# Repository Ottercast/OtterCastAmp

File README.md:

# OtterCastAmp

OtterCastAmp is an open-source Sonos Amp replacement, based on a Sochip S3 SoC and pulseaudio sink/source.

## How do I get one?

We are currently planning a small batch production run, stay tuned.
[editors notes: It is 2024 now and noone really expected how bad covid would affect the supply chain. While all parts are available again, we are only slowly getting interested in this project again]

You don't want to wait? You can of course run a small batch on your own! Please have a look into the [gerber folder](/gerber_v1.2), a batch size of just 5 (and up to 30) boards is supported by JLC.

## Installation & Configuration

After [downloading and flashing](https://cast.otter.jetzt/docs/firmware/#download-ready-made-images) the image, OtterCastAmp can either be configured via the `config.ini` file or via the web-interface.

Check out our [Documentation](https://cast.otter.jetzt/docs/) for more information!

## Schematics?

[Schematics!](/schematic_V1.2/OtterCastAmp.pdf)

## Team

 - [@lucysrausch](https://bsky.app/profile/lucysrausch.bsky.social) Hardware - OtterCastAmp
 - [@_Jana_Marie](https://twitter.com/_Jana_Marie) Hardware - OtterCastAudio
 - [@Toble_Miner](https://twitter.com/Toble_Miner) Software - Embedded Linux
 - [@Manawyrm](https://twitter.com/Manawyrm) Software - Frontend & OTA

## Do you plan a PoE version?

Maybe.
(25W of power is not enough and >50W isn't popular)

## Status

HW v1.0 is ordered and we already found bugs fixed in v1.2 (not ordered yet)
Tested & working:

 - [x] Audio Speaker Out
 - [x] Audio Line In
 - [ ] Bluetooth Audio In
 - [x] USB PD
 - [x] WiFi
 - [x] Ethernet
 - [x] Display
 - [x] Uart

 - [x] Webinterface (config)
 - [x] Shairport-sync
 - [x] Pulseaudio sink
 - [x] Pulseaudio source
 - [x] snapcast

## License

Note: The following files or directories are excluded from the License and are otherwise licensed

 - 3D/
 - datasheets/

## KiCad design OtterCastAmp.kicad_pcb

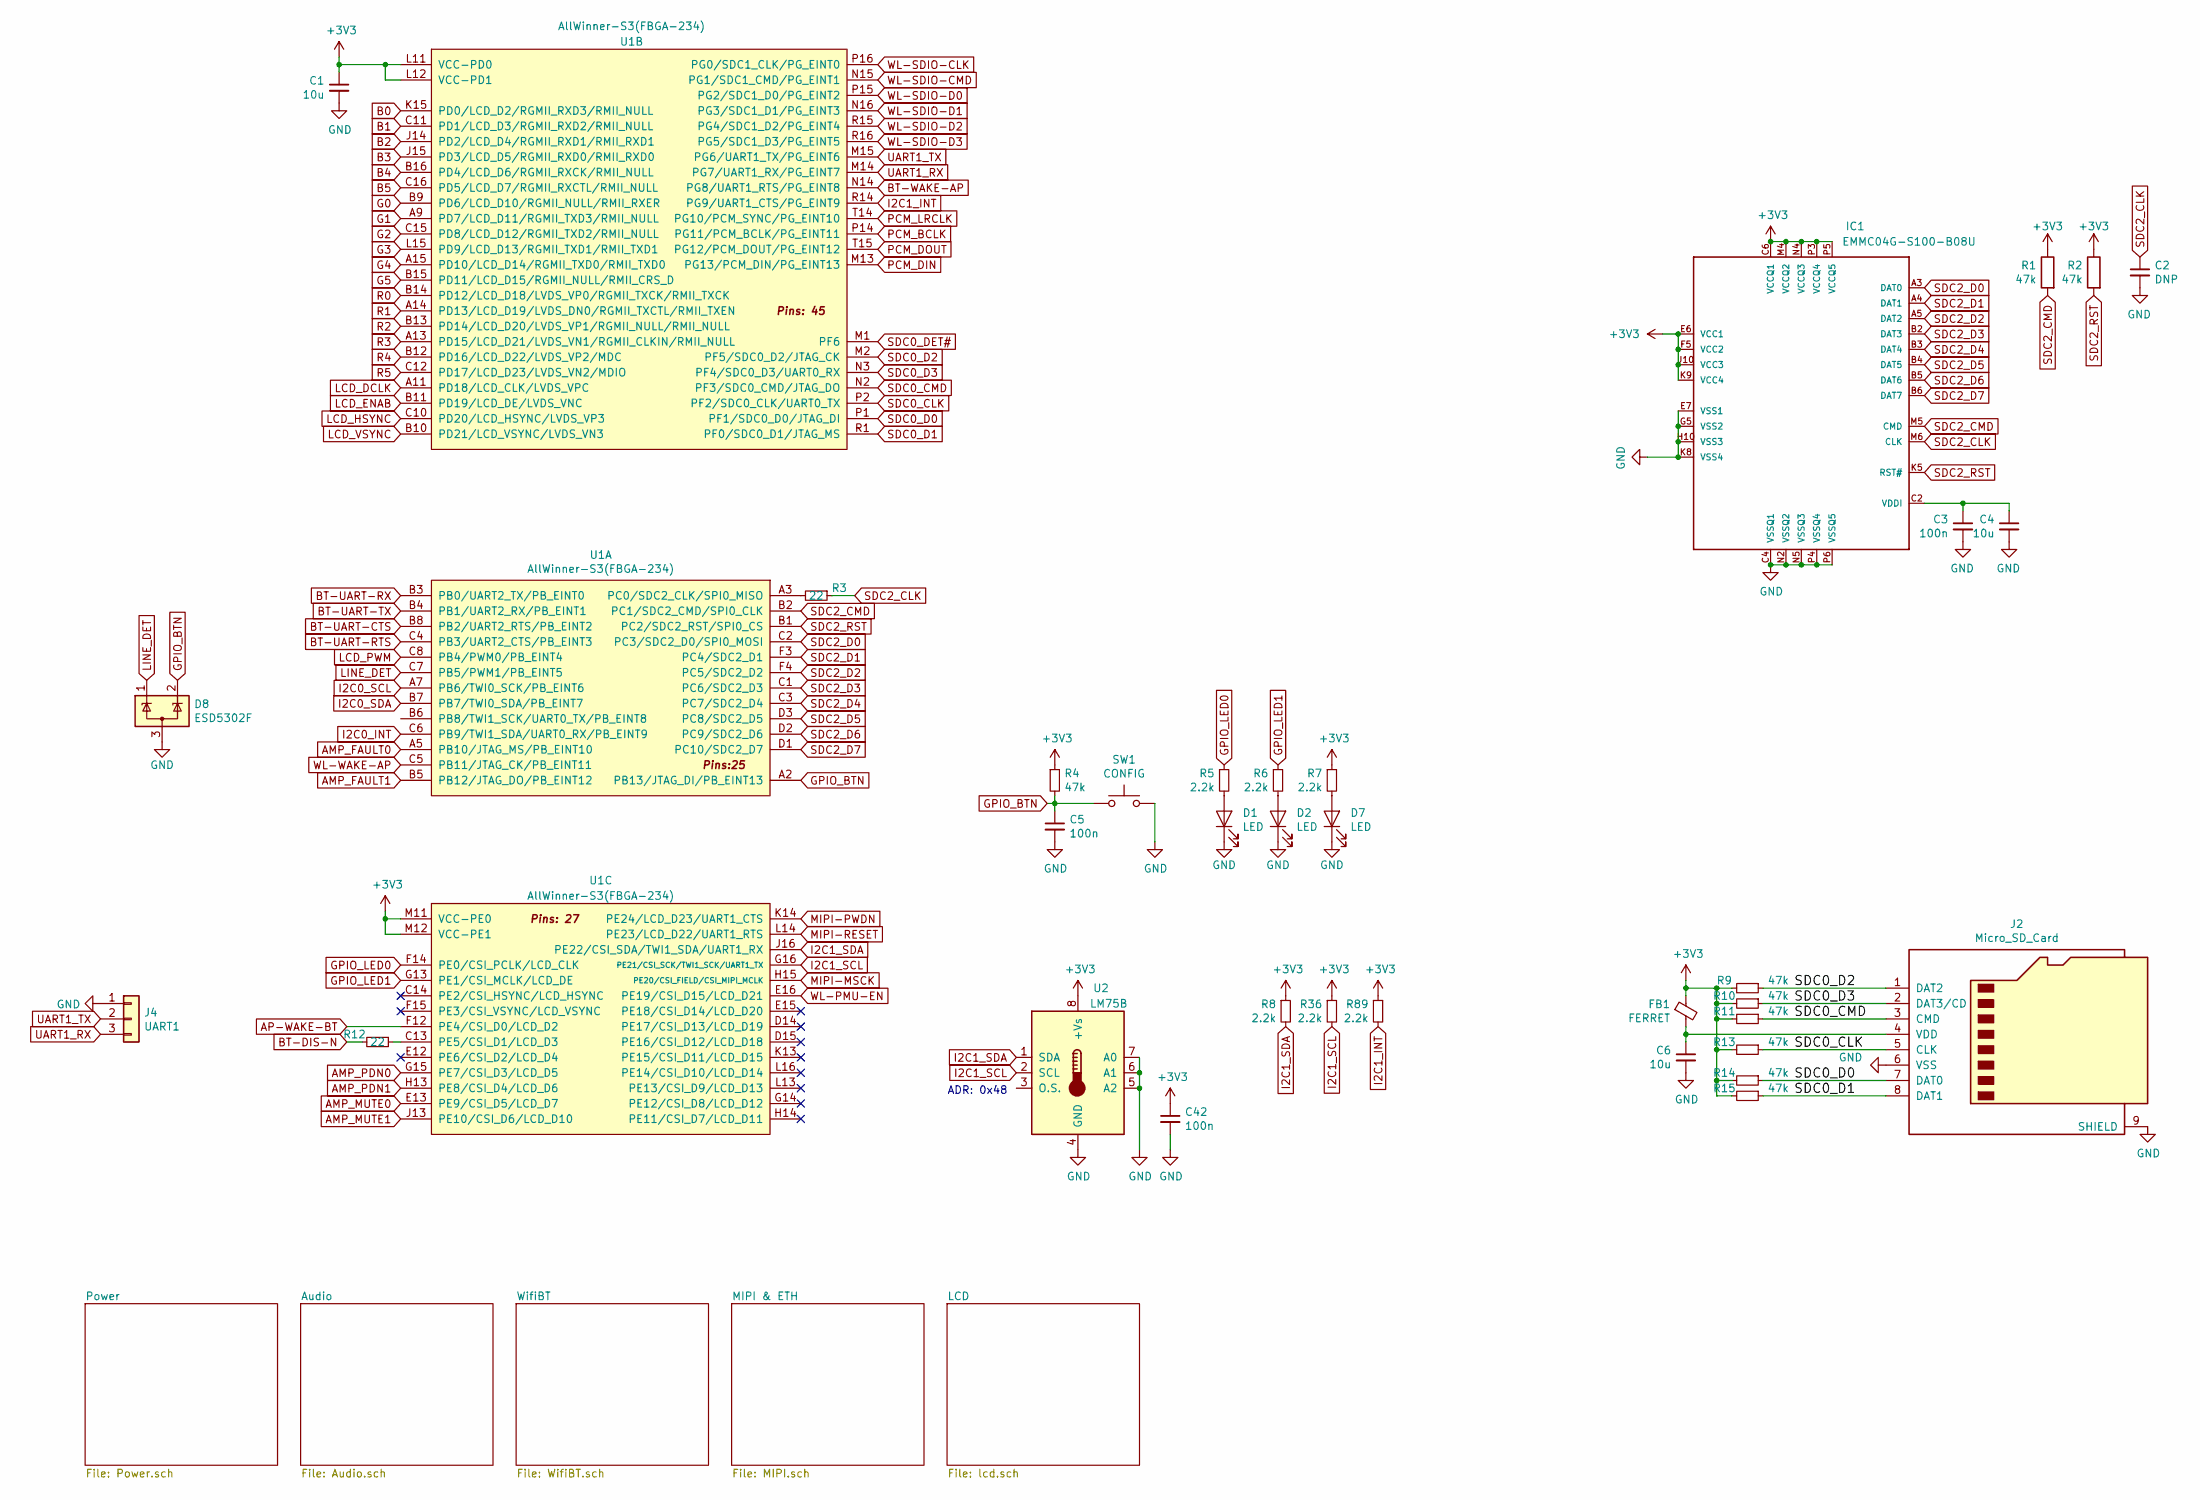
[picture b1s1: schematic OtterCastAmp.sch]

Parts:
C1, C4, C6: 10u; C_0603
C2: DNP; C_0402
C3, C5, C42: 100n; C_0402
D1, D2, D7: LED; LED_0603_1608Metric
D8: ESD5302F; SOT-23
FB1: FERRET; R_0805
IC1: EMMC04G-S100-B08U; MICRON_EMMC_153
J2: Micro_SD_Card; SUNTECH_ST-TF-003A
J4: UART1; PinHeader_1x03_P2.54mm_Vertical
R1, R2, R4, R9, R10, R11, R13, R14, R15: 47k; R_0402
R3, R12: 22; R_0402
R5, R6, R7, R8, R36, R89: 2.2k; R_0402
SW1: CONFIG; SW_SPST_EVQP7C
U1: AllWinner-S3(FBGA-234); FBGA-234(Pitch-0.65mm_Pad-0.3mm_11x11x1.08mm)
U2: LM75B; VSSOP-8_3.0x3.0mm_P0.65mm

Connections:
AMP_FAULT0: U1.A5 (PB10/JTAG_MS/PB_EINT10); also elsewhere on the board
AMP_FAULT1: U1.B5 (PB12/JTAG_DO/PB_EINT12); also elsewhere on the board
AMP_MUTE0: U1.E13 (PE9/CSI_D5/LCD_D7); also elsewhere on the board
AMP_MUTE1: U1.J13 (PE10/CSI_D6/LCD_D10); also elsewhere on the board
AMP_PDN0: U1.G15 (PE7/CSI_D3/LCD_D5); also elsewhere on the board
AMP_PDN1: U1.H13 (PE8/CSI_D4/LCD_D6); also elsewhere on the board
AP-WAKE-BT: U1.F12 (PE4/CSI_D0/LCD_D2); also elsewhere on the board
B0: U1.K15 (PD0/LCD_D2/RGMII_RXD3/RMII_NULL)
B1: U1.C11 (PD1/LCD_D3/RGMII_RXD2/RMII_NULL); also elsewhere on the board
B2: U1.J14 (PD2/LCD_D4/RGMII_RXD1/RMII_RXD1); also elsewhere on the board
B3: U1.J15 (PD3/LCD_D5/RGMII_RXD0/RMII_RXD0); also elsewhere on the board
B4: U1.B16 (PD4/LCD_D6/RGMII_RXCK/RMII_NULL); also elsewhere on the board
B5: U1.C16 (PD5/LCD_D7/RGMII_RXCTL/RMII_NULL); also elsewhere on the board
BT-DIS-N: R12.2; also elsewhere on the board
BT-UART-CTS: U1.B8 (PB2/UART2_RTS/PB_EINT2); also elsewhere on the board
BT-UART-RTS: U1.C4 (PB3/UART2_CTS/PB_EINT3); also elsewhere on the board
BT-UART-RX: U1.B3 (PB0/UART2_TX/PB_EINT0); also elsewhere on the board
BT-UART-TX: U1.B4 (PB1/UART2_RX/PB_EINT1); also elsewhere on the board
BT-WAKE-AP: U1.N14 (PG8/UART1_RTS/PG_EINT8); also elsewhere on the board
G0: U1.B9 (PD6/LCD_D10/RGMII_NULL/RMII_RXER); also elsewhere on the board
G1: U1.A9 (PD7/LCD_D11/RGMII_TXD3/RMII_NULL); also elsewhere on the board
G2: U1.C15 (PD8/LCD_D12/RGMII_TXD2/RMII_NULL); also elsewhere on the board
G3: U1.L15 (PD9/LCD_D13/RGMII_TXD1/RMII_TXD1); also elsewhere on the board
G4: U1.A15 (PD10/LCD_D14/RGMII_TXD0/RMII_TXD0); also elsewhere on the board
G5: U1.B15 (PD11/LCD_D15/RGMII_NULL/RMII_CRS_D); also elsewhere on the board
GND: C1.2, C2.2, C3.2, C4.2, C5.2, C6.2, C42.2, D1.1 (K), D2.1 (K), D7.1 (K), D8.3 (A), IC1.C4 (VSSQ1), IC1.E7 (VSS1), IC1.G5 (VSS2), IC1.H10 (VSS3), IC1.K8 (VSS4), IC1.N2 (VSSQ2), IC1.N5 (VSSQ3), IC1.P4 (VSSQ4), IC1.P6 (VSSQ5), J2.6 (VSS), J2.9 (SHIELD), J4.1, SW1.2, U2.4 (GND), U2.5 (A2), U2.6 (A1), U2.7 (A0); also elsewhere on the board
GPIO_BTN: C5.1, D8.2 (K), R4.2, SW1.1, U1.A2 (PB13/JTAG_DI/PB_EINT13); also elsewhere on the board
GPIO_LED0: R5.1, U1.F14 (PE0/CSI_PCLK/LCD_CLK); also elsewhere on the board
GPIO_LED1: R6.1, U1.G13 (PE1/CSI_MCLK/LCD_DE); also elsewhere on the board
I2C0_INT: U1.C6 (PB9/TWI1_SDA/UART0_RX/PB_EINT9); also elsewhere on the board
I2C0_SCL: U1.A7 (PB6/TWI0_SCK/PB_EINT6); also elsewhere on the board
I2C0_SDA: U1.B7 (PB7/TWI0_SDA/PB_EINT7); also elsewhere on the board
I2C1_INT: R89.2, U1.R14 (PG9/UART1_CTS/PG_EINT9); also elsewhere on the board
I2C1_SCL: R36.2, U1.G16 (PE21/CSI_SCK/TWI1_SCK/UART1_TX), U2.2 (SCL); also elsewhere on the board
I2C1_SDA: R8.2, U1.J16 (PE22/CSI_SDA/TWI1_SDA/UART1_RX), U2.1 (SDA); also elsewhere on the board
LCD_DCLK: U1.A11 (PD18/LCD_CLK/LVDS_VPC); also elsewhere on the board
LCD_ENAB: U1.B11 (PD19/LCD_DE/LVDS_VNC); also elsewhere on the board
LCD_HSYNC: U1.C10 (PD20/LCD_HSYNC/LVDS_VP3); also elsewhere on the board
LCD_PWM: U1.C8 (PB4/PWM0/PB_EINT4); also elsewhere on the board
LCD_VSYNC: U1.B10 (PD21/LCD_VSYNC/LVDS_VN3); also elsewhere on the board
LINE_DET: D8.1 (K), U1.C7 (PB5/PWM1/PB_EINT5); also elsewhere on the board
MIPI-MSCK: U1.H15 (PE20/CSI_FIELD/CSI_MIPI_MCLK)
MIPI-PWDN: U1.K14 (PE24/LCD_D23/UART1_CTS)
MIPI-RESET: U1.L14 (PE23/LCD_D22/UART1_RTS)
unnamed: C3.1, C4.1, IC1.C2 (VDDI)
unnamed: C6.1, FB1.2, J2.4 (VDD)
unnamed: D1.2 (A), R5.2
unnamed: D2.2 (A), R6.2
unnamed 141: D7.2 (A), R7.2; also elsewhere on the board
unnamed: R3.2, U1.A3 (PC0/SDC2_CLK/SPI0_MISO)
unnamed: R12.1, U1.C13 (PE5/CSI_D1/LCD_D3)
PCM_BCLK: U1.P14 (PG11/PCM_BCLK/PG_EINT11); also elsewhere on the board
PCM_DIN: U1.M13 (PG13/PCM_DIN/PG_EINT13); also elsewhere on the board
PCM_DOUT: U1.T15 (PG12/PCM_DOUT/PG_EINT12); also elsewhere on the board
PCM_LRCLK: U1.T14 (PG10/PCM_SYNC/PG_EINT10); also elsewhere on the board
R0: U1.B14 (PD12/LCD_D18/LVDS_VP0/RGMII_TXCK/RMII_T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)
R1: U1.A14 (PD13/LCD_D19/LVDS_DN0/RGMII_TXCTL/RMII_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); also elsewhere on the board
R2: U1.B13 (PD14/LCD_D20/LVDS_VP1/RGMII_NULL/RMII_N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); also elsewhere on the board
R3: U1.A13 (PD15/LCD_D21/LVDS_VN1/RGMII_CLKIN/RMII_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); also elsewhere on the board
R4: U1.B12 (PD16/LCD_D22/LVDS_VP2/MDC); also elsewhere on the board
R5: U1.C12 (PD17/LCD_D23/LVDS_VN2/MDIO); also elsewhere on the board
SDC0_CLK: J2.5 (CLK), R13.1, U1.P2 (PF2/SDC0_CLK/UART0_TX)
SDC0_CMD: J2.3 (CMD), R11.1, U1.N2 (PF3/SDC0_CMD/JTAG_DO)
SDC0_D0: J2.7 (DAT0), R14.1, U1.P1 (PF1/SDC0_D0/JTAG_DI)
SDC0_D1: J2.8 (DAT1), R15.1, U1.R1 (PF0/SDC0_D1/JTAG_MS)
SDC0_D2: J2.1 (DAT2), R9.1, U1.M2 (PF5/SDC0_D2/JTAG_CK)
SDC0_D3: J2.2 (DAT3/CD), R10.1, U1.N3 (PF4/SDC0_D3/UART0_RX)
SDC0_DET#: U1.M1 (PF6)
SDC2_CLK: C2.1, IC1.M6 (CLK), R3.1
SDC2_CMD: IC1.M5 (CMD), R1.2, U1.B2 (PC1/SDC2_CMD/SPI0_CLK)
SDC2_D0: IC1.A3 (DAT0), U1.C2 (PC3/SDC2_D0/SPI0_MOSI)
SDC2_D1: IC1.A4 (DAT1), U1.F3 (PC4/SDC2_D1)
SDC2_D2: IC1.A5 (DAT2), U1.F4 (PC5/SDC2_D2)
SDC2_D3: IC1.B2 (DAT3), U1.C1 (PC6/SDC2_D3)
SDC2_D4: IC1.B3 (DAT4), U1.C3 (PC7/SDC2_D4)
SDC2_D5: IC1.B4 (DAT5), U1.D3 (PC8/SDC2_D5)
SDC2_D6: IC1.B5 (DAT6), U1.D2 (PC9/SDC2_D6)
SDC2_D7: IC1.B6 (DAT7), U1.D1 (PC10/SDC2_D7)
SDC2_RST: IC1.K5 (RST#), R2.2, U1.B1 (PC2/SDC2_RST/SPI0_CS)
UART1_RX: J4.3, U1.M14 (PG7/UART1_RX/PG_EINT7)
UART1_TX: J4.2, U1.M15 (PG6/UART1_TX/PG_EINT6)
WL-PMU-EN: U1.E16 (PE19/CSI_D15/LCD_D21); also elsewhere on the board
WL-SDIO-CLK: U1.P16 (PG0/SDC1_CLK/PG_EINT0); also elsewhere on the board
WL-SDIO-CMD: U1.N15 (PG1/SDC1_CMD/PG_EINT1); also elsewhere on the board
WL-SDIO-D0: U1.P15 (PG2/SDC1_D0/PG_EINT2); also elsewhere on the board
WL-SDIO-D1: U1.N16 (PG3/SDC1_D1/PG_EINT3); also elsewhere on the board
WL-SDIO-D2: U1.R15 (PG4/SDC1_D2/PG_EINT4); also elsewhere on the board
WL-SDIO-D3: U1.R16 (PG5/SDC1_D3/PG_EINT5); also elsewhere on the board
WL-WAKE-AP: U1.C5 (PB11/JTAG_CK/PB_EINT11); also elsewhere on the board

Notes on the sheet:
ADR: 0x48

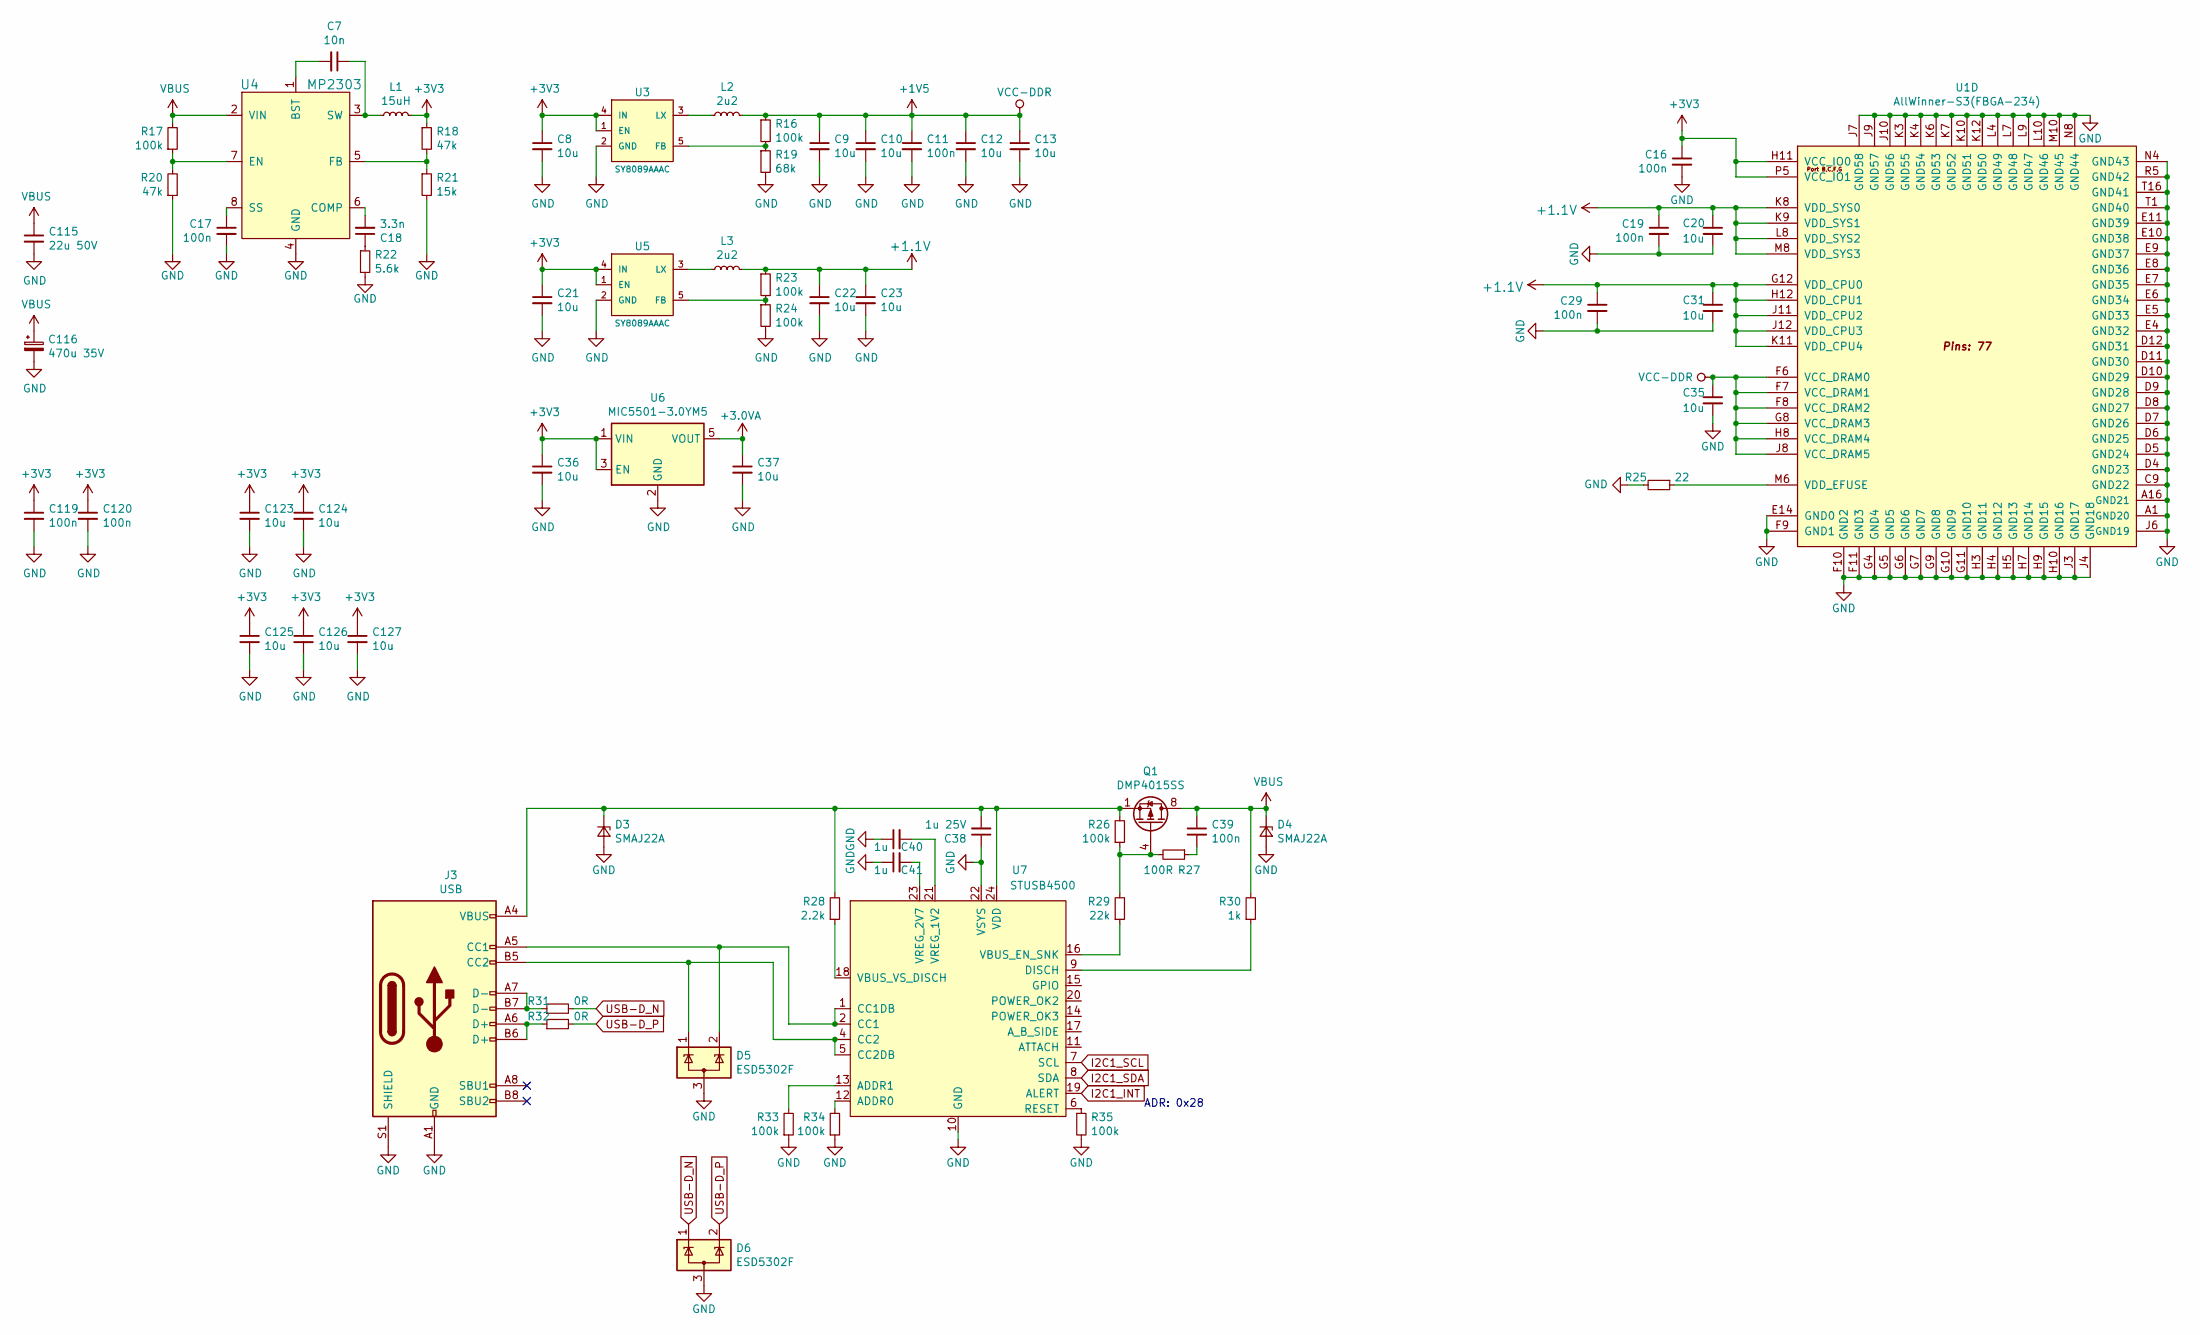
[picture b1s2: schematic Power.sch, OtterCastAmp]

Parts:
C7: 10n; C_0402
C8, C9, C10, C12, C13, C20, C21, C22, C23, C31, C35, C36, C37, C123, C124, C125, C126, C127: 10u; C_0603
C11, C16, C17, C19, C29, C39, C119, C120: 100n; C_0402
C18: 3.3n; C_0402
C38: 1u 25V; C_0603
C40, C41: 1u; C_0402
C115: 22u 50V; C_1206_3216Metric
C116: 470u 35V; CP_Elec_10x10.5
D3, D4: SMAJ22A; D_SMA
D5, D6: ESD5302F; SOT-23
J3: USB; USB-C 16Pin
L1: 15uH; L_10.4x10.4_H4.8
L2, L3: 2u2; Inductor_4040
Q1: DMP4015SS; SOIC-8_3.9x4.9mm_P1.27mm
R16, R17, R23, R24, R26, R33, R34, R35: 100k; R_0402
R18, R20: 47k; R_0402
R19: 68k; R_0402
R21: 15k; R_0402
R22: 5.6k; R_0402
R25: 22; R_0402
R27: 100R; R_0402
R28: 2.2k; R_0402
R29: 22k; R_0402
R30: 1k; R_0402
R31, R32: 0R; R_0402
U1: AllWinner-S3(FBGA-234); FBGA-234(Pitch-0.65mm_Pad-0.3mm_11x11x1.08mm)
U3, U5: SY8089AAAC; SOT-23-5
U4: MP2303; SOIC-8-1EP_3.9x4.9mm_P1.27mm_EP2.29x3mm
U6: MIC5501-3.0YM5; SOT-23-5
U7: STUSB4500; QFN-24-1EP_4x4mm_P0.5mm_EP2.7x2.7mm

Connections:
+1.1V: C19.1, C20.1, C22.1, C23.1, C29.1, C31.1, L3.2, R23.1, U1.G12 (VDD_CPU0), U1.H12 (VDD_CPU1), U1.J11 (VDD_CPU2), U1.J12 (VDD_CPU3), U1.K8 (VDD_SYS0), U1.K9 (VDD_SYS1), U1.K11 (VDD_CPU4), U1.L8 (VDD_SYS2), U1.M8 (VDD_SYS3); also elsewhere on the board
+1V5: C9.1, C10.1, C11.1, C12.1, C13.1, C35.1, L2.2, R16.1, U1.F6 (VCC_DRAM0), U1.F7 (VCC_DRAM1), U1.F8 (VCC_DRAM2), U1.G8 (VCC_DRAM3), U1.H8 (VCC_DRAM4), U1.J8 (VCC_DRAM5); also elsewhere on the board
+3.0VA: C37.1, U6.5 (VOUT); also elsewhere on the board
GND: C8.2, C9.2, C10.2, C11.2, C12.2, C13.2, C16.2, C17.2, C19.2, C20.2, C21.2, C22.2, C23.2, C29.2, C31.2, C35.2, C36.2, C37.2, C38.1, C40.1, C41.1, C115.2, C116.2, C119.2, C120.2, C123.2, C124.2, C125.2, C126.2, C127.2, D3.2 (A), D4.2 (A), D5.3 (A), D6.3 (A), J3.A1 (GND), J3.A12 (GND), J3.B1 (GND), J3.B12 (GND), J3.S1 (SHIELD), R19.2, R20.1, R21.2, R22.2, R24.2, R25.2, R33.1, R34.1, R35.2, U1.A1 (GND20), U1.A16 (GND21), U1.C9 (GND22), U1.D4 (GND23), U1.D5 (GND24), U1.D6 (GND25), U1.D7 (GND26), U1.D8 (GND27), U1.D9 (GND28), U1.D10 (GND29), U1.D11 (GND30), U1.D12 (GND31), U1.E4 (GND32), U1.E5 (GND33), U1.E6 (GND34), U1.E7 (GND35), U1.E8 (GND36), U1.E9 (GND37), U1.E10 (GND38), U1.E11 (GND39), U1.E14 (GND0), U1.F9 (GND1), U1.F10 (GND2), U1.F11 (GND3), U1.G4 (GND4), U1.G5 (GND5), U1.G6 (GND6), U1.G7 (GND7), U1.G9 (GND8), U1.G10 (GND9), U1.G11 (GND10), U1.H3 (GND11), U1.H4 (GND12), U1.H5 (GND13), U1.H7 (GND14), U1.H9 (GND15), U1.H10 (GND16), U1.J3 (GND17), U1.J4 (GND18), U1.J6 (GND19), U1.J7 (GND58), U1.J9 (GND57), U1.J10 (GND56), U1.K3 (GND55), U1.K4 (GND54), U1.K6 (GND53), U1.K7 (GND52), U1.K10 (GND51), U1.K12 (GND50), U1.L4 (GND49), U1.L7 (GND48), U1.L9 (GND47), U1.L10 (GND46), U1.M10 (GND45), U1.N4 (GND43), U1.N8 (GND44), U1.R5 (GND42), U1.T1 (GND40), U1.T16 (GND41), U3.2 (GND), U4.4 (GND), U4.9 (GND), U5.2 (GND), U6.2 (GND), U7.10 (GND), U7.22 (VSYS), U7.25 (GND); also elsewhere on the board
I2C1_INT: U7.19 (ALERT); also elsewhere on the board
I2C1_SCL: U7.7 (SCL); also elsewhere on the board
I2C1_SDA: U7.8 (SDA); also elsewhere on the board
unnamed: C7.1, L1.1, U4.3 (SW)
unnamed: C7.2, U4.1 (BST)
unnamed: C17.1, U4.8 (SS)
unnamed: C18.1, R22.1
unnamed: C18.2, U4.6 (COMP)
unnamed: C38.2, D3.1 (K), J3.A4 (VBUS), J3.A9 (VBUS), J3.B4 (VBUS), J3.B9 (VBUS), Q1.1 (S), Q1.2 (S), Q1.3 (S), R26.2, R28.2, U7.24 (VDD)
unnamed: C39.2, R27.1
unnamed: C40.2, U7.21 (VREG_1V2)
unnamed: C41.2, U7.23 (VREG_2V7)
unnamed: D5.1 (K), J3.B5 (CC2), U7.4 (CC2), U7.5 (CC2DB)
unnamed: D5.2 (K), J3.A5 (CC1), U7.1 (CC1DB), U7.2 (CC1)
unnamed: J3.A6 (D+), J3.B6 (D+), R32.1
unnamed: J3.A7 (D-), J3.B7 (D-), R31.1
unnamed: L2.1, U3.3 (LX)
unnamed: L3.1, U5.3 (LX)
unnamed: Q1.4 (G), R26.1, R27.2, R29.2
unnamed: R16.2, R19.1, U3.5 (FB)
unnamed: R17.1, R20.2, U4.7 (EN)
unnamed: R18.2, R21.1, U4.5 (FB)
unnamed: R23.2, R24.1, U5.5 (FB)
unnamed: R25.1, U1.M6 (VDD_EFUSE)
unnamed: R28.1, U7.18 (VBUS_VS_DISCH)
unnamed: R29.1, U7.16 (VBUS_EN_SNK)
unnamed: R30.1, U7.9 (DISCH)
unnamed: R33.2, U7.13 (ADDR1)
unnamed: R34.2, U7.12 (ADDR0)
unnamed: R35.1, U7.6 (RESET)
USB-D_N: D6.1 (K), R31.2; also elsewhere on the board
USB-D_P: D6.2 (K), R32.2; also elsewhere on the board
VBUS: C39.1, C115.1, C116.1, D4.1 (K), Q1.5 (D), Q1.6 (D), Q1.7 (D), Q1.8 (D), R17.2, R30.2, U4.2 (VIN); also elsewhere on the board

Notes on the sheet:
ADR: 0x28

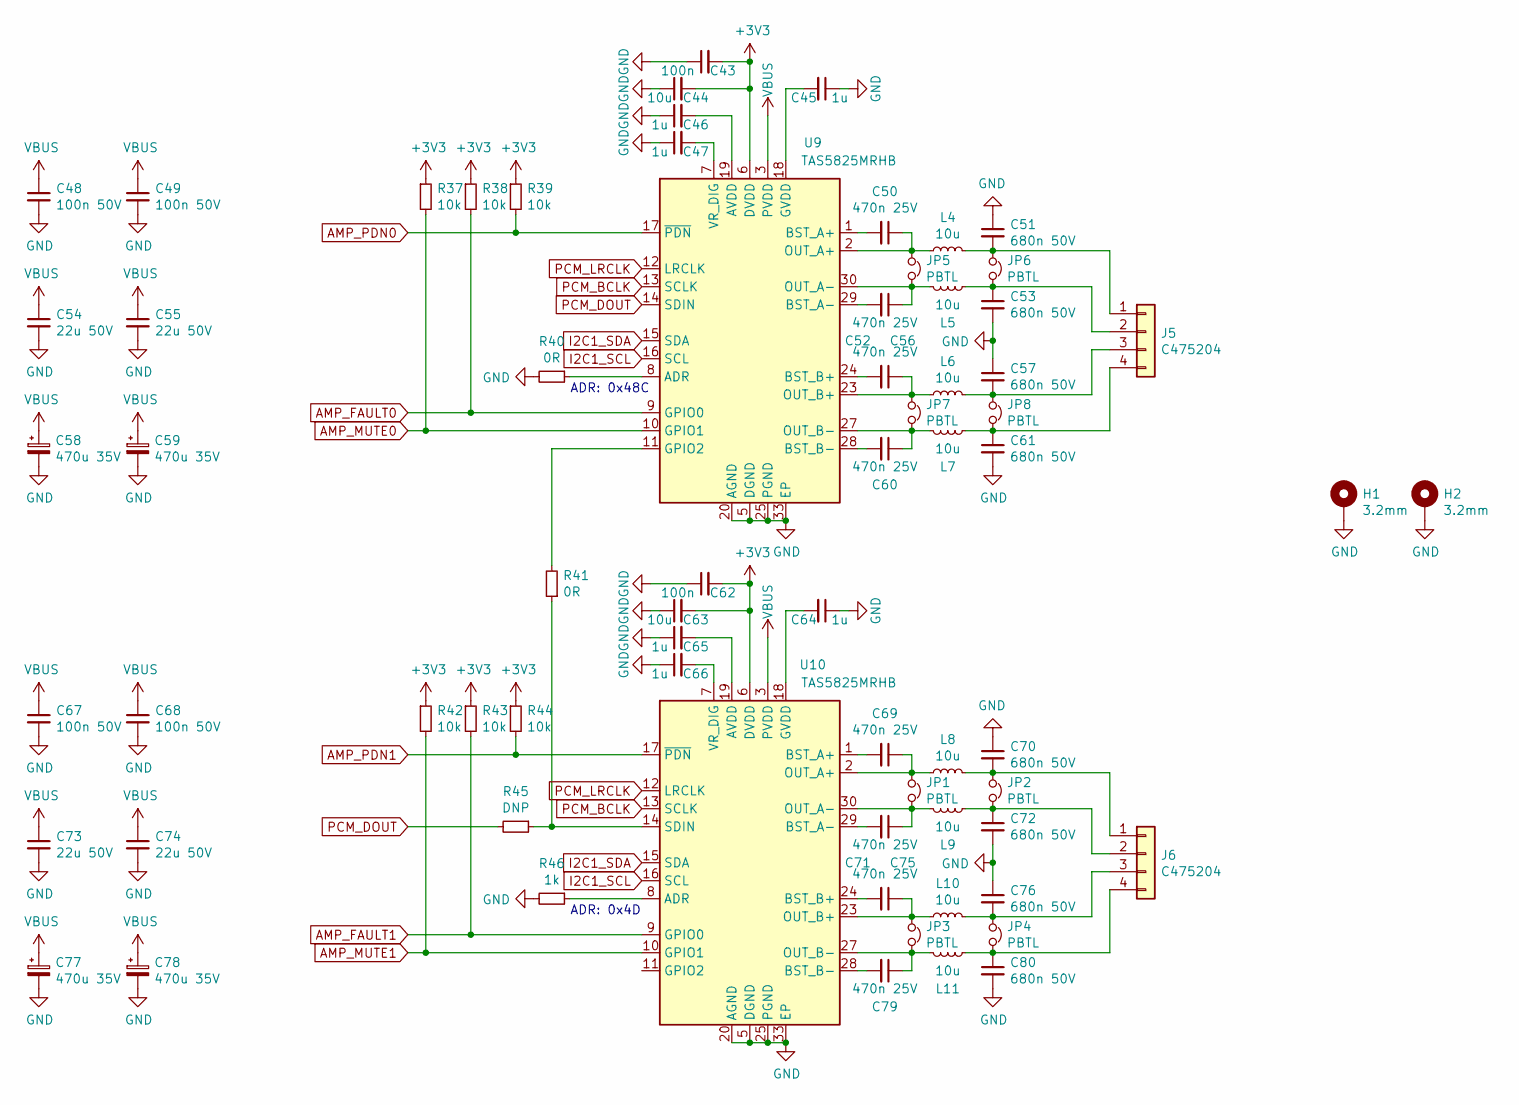
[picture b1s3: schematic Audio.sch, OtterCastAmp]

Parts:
C43, C62: 100n; C_0402
C44, C63: 10u; C_0603
C45, C46, C47, C64, C65, C66: 1u; C_0402
C48, C49, C67, C68: 100n 50V; C_0603
C50, C52, C56, C60, C69, C71, C75, C79: 470n 25V; C_0603
C51, C53, C57, C61, C70, C72, C76, C80: 680n 50V; C_1206_3216Metric
C54, C55, C73, C74: 22u 50V; C_1206_3216Metric
C58, C59, C77, C78: 470u 35V; CP_Elec_10x10.5
H1, H2: 3.2mm; MountingHole_3.2mm_M3_Pad_Via
J5, J6: C475204
JP1, JP2, JP3, JP4, JP5, JP6, JP7, JP8: PBTL; SolderJumper-2_P1.3mm_Open_Pad1.0x1.5mm
L4, L5, L6, L7, L8, L9, L10, L11: 10u; L_10.4x10.4_H4.8
R37, R38, R39, R42, R43, R44: 10k; R_0402
R40, R41: 0R; R_0402
R45: DNP; R_0402
R46: 1k; R_0402
U9, U10: TAS5825MRHB; Texas_S-PVQFN-N32_EP3.45x3.45mm

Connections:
AMP_FAULT0: R38.2, U9.9 (GPIO0); also elsewhere on the board
AMP_FAULT1: R43.2, U10.9 (GPIO0); also elsewhere on the board
AMP_MUTE0: R37.2, U9.10 (GPIO1); also elsewhere on the board
AMP_MUTE1: R42.2, U10.10 (GPIO1); also elsewhere on the board
AMP_PDN0: R39.2, U9.17 (~PDN); also elsewhere on the board
AMP_PDN1: R44.2, U10.17 (~PDN); also elsewhere on the board
GND: C43.1, C44.1, C45.1, C46.1, C47.1, C48.2, C49.2, C51.1, C53.2, C54.2, C55.2, C57.1, C58.2, C59.2, C61.2, C62.1, C63.1, C64.1, C65.1, C66.1, C67.2, C68.2, C70.1, C72.2, C73.2, C74.2, C76.1, C77.2, C78.2, C80.2, H1.1, H2.1, R40.2, R46.2, U9.5 (DGND), U9.20 (AGND), U9.25 (PGND), U9.26 (PGND), U9.31 (PGND), U9.32 (PGND), U9.33 (EP), U10.5 (DGND), U10.20 (AGND), U10.25 (PGND), U10.26 (PGND), U10.31 (PGND), U10.32 (PGND), U10.33 (EP); also elsewhere on the board
I2C1_SCL: U9.16 (SCL), U10.16 (SCL); also elsewhere on the board
I2C1_SDA: U9.15 (SDA), U10.15 (SDA); also elsewhere on the board
unnamed: C45.2, U9.18 (GVDD)
unnamed: C46.2, U9.19 (AVDD)
unnamed: C47.2, U9.7 (VR_DIG)
unnamed: C50.1, JP5.1, L4.1, U9.2 (OUT_A+)
unnamed: C50.2, U9.1 (BST_A+)
unnamed: C51.2, J5.1, JP6.1, L4.2
unnamed: C52.1, JP5.2, L5.2, U9.30 (OUT_A-)
unnamed: C52.2, U9.29 (BST_A-)
unnamed: C53.1, J5.2, JP6.2, L5.1
unnamed: C56.1, JP7.1, L6.1, U9.23 (OUT_B+)
unnamed: C56.2, U9.24 (BST_B+)
unnamed: C57.2, J5.3, JP8.1, L6.2
unnamed: C60.1, JP7.2, L7.2, U9.27 (OUT_B-)
unnamed: C60.2, U9.28 (BST_B-)
unnamed: C61.1, J5.4, JP8.2, L7.1
unnamed: C64.2, U10.18 (GVDD)
unnamed: C65.2, U10.19 (AVDD)
unnamed: C66.2, U10.7 (VR_DIG)
unnamed: C69.1, JP1.1, L8.1, U10.2 (OUT_A+)
unnamed: C69.2, U10.1 (BST_A+)
unnamed: C70.2, J6.1, JP2.1, L8.2
unnamed: C71.1, JP1.2, L9.2, U10.30 (OUT_A-)
unnamed: C71.2, U10.29 (BST_A-)
unnamed: C72.1, J6.2, JP2.2, L9.1
unnamed: C75.1, JP3.1, L10.1, U10.23 (OUT_B+)
unnamed: C75.2, U10.24 (BST_B+)
unnamed: C76.2, J6.3, JP4.1, L10.2
unnamed: C79.1, JP3.2, L11.2, U10.27 (OUT_B-)
unnamed: C79.2, U10.28 (BST_B-)
unnamed: C80.1, J6.4, JP4.2, L11.1
unnamed: R40.1, U9.8 (ADR)
unnamed: R41.1, R45.1, U10.14 (SDIN)
unnamed: R41.2, U9.11 (GPIO2)
unnamed: R46.1, U10.8 (ADR)
PCM_BCLK: U9.13 (SCLK), U10.13 (SCLK); also elsewhere on the board
PCM_DOUT: R45.2, U9.14 (SDIN); also elsewhere on the board
PCM_LRCLK: U9.12 (LRCLK), U10.12 (LRCLK); also elsewhere on the board
VBUS: C48.1, C49.1, C54.1, C55.1, C58.1, C59.1, C67.1, C68.1, C73.1, C74.1, C77.1, C78.1, U9.3 (PVDD), U9.4 (PVDD), U9.21 (PVDD), U9.22 (PVDD), U10.3 (PVDD), U10.4 (PVDD), U10.21 (PVDD), U10.22 (PVDD); also elsewhere on the board

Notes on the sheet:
ADR: 0x48C
ADR: 0x4D

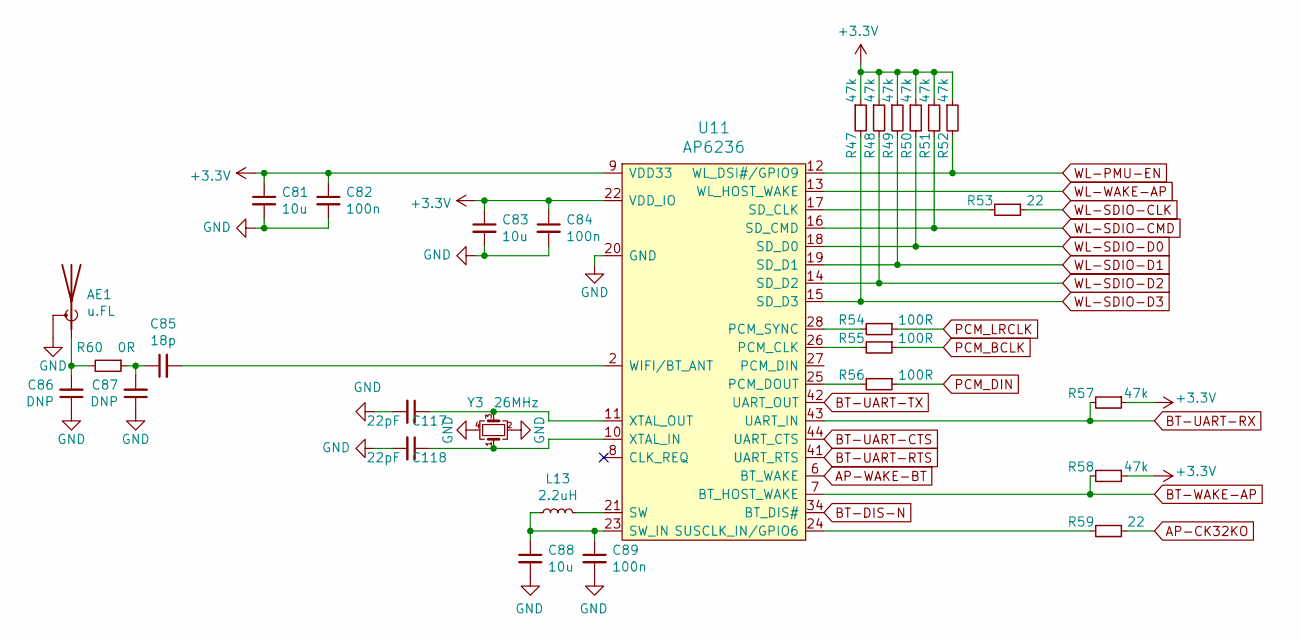
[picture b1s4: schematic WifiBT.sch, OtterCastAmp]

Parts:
AE1: u.FL; U.FL_Molex_MCRF_73412-0110_Vertical
C81, C83, C88: 10u; C_0603
C82, C84, C89: 100n; C_0402
C85: 18p; C_0402
C86, C87: DNP; C_0402
C117, C118: 22pF; C_0402
L13: 2.2uH; Inductor_4040; LCSC C167747
R47, R48, R49, R50, R51, R52, R57, R58: 47k; R_0402
R53, R59: 22; R_0402
R54, R55, R56: 100R; R_0402
R60: 0R; R_0402
U11: AP6236; LGA_44_12x12mm_0.9mm
Y3: 26MHz; Oscillator_3225

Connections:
AP-CK32KO: R59.1; also elsewhere on the board
AP-WAKE-BT: U11.6 (BT_WAKE); also elsewhere on the board
BT-DIS-N: U11.34 (BT_DIS#); also elsewhere on the board
BT-UART-CTS: U11.44 (UART_CTS); also elsewhere on the board
BT-UART-RTS: U11.41 (UART_RTS); also elsewhere on the board
BT-UART-RX: R57.2, U11.43 (UART_IN); also elsewhere on the board
BT-UART-TX: U11.42 (UART_OUT); also elsewhere on the board
BT-WAKE-AP: R58.2, U11.7 (BT_HOST_WAKE); also elsewhere on the board
GND: AE1.2 (Shield), C81.2, C82.2, C83.2, C84.2, C86.1, C87.1, C88.2, C89.2, C117.2, C118.2, U11.1 (GND), U11.20 (GND), U11.31 (GND), U11.33 (GND), U11.36 (GND), Y3.2, Y3.4; also elsewhere on the board
unnamed: AE1.1 (A), C86.2, R60.2
unnamed: C85.1, C87.2, R60.1
unnamed: C85.2, U11.2 (WIFI/BT_ANT)
unnamed: C88.1, C89.1, L13.1, U11.23 (SW_IN)
unnamed: C117.1, U11.11 (XTAL_OUT), Y3.3
unnamed: C118.1, U11.10 (XTAL_IN), Y3.1
unnamed: L13.2, U11.21 (SW)
unnamed: R53.2, U11.17 (SD_CLK)
unnamed: R54.2, U11.28 (PCM_SYNC)
unnamed: R55.2, U11.26 (PCM_CLK)
unnamed: R56.2, U11.25 (PCM_DOUT)
unnamed: R59.2, U11.24 (SUSCLK_IN/GPIO6)
PCM_BCLK: R55.1; also elsewhere on the board
PCM_DIN: R56.1; also elsewhere on the board
PCM_LRCLK: R54.1; also elsewhere on the board
WL-PMU-EN: R52.2, U11.12 (WL_DSI#/GPIO9); also elsewhere on the board
WL-SDIO-CLK: R53.1; also elsewhere on the board
WL-SDIO-CMD: R51.2, U11.16 (SD_CMD); also elsewhere on the board
WL-SDIO-D0: R50.2, U11.18 (SD_D0); also elsewhere on the board
WL-SDIO-D1: R49.2, U11.19 (SD_D1); also elsewhere on the board
WL-SDIO-D2: R48.2, U11.14 (SD_D2); also elsewhere on the board
WL-SDIO-D3: R47.2, U11.15 (SD_D3); also elsewhere on the board
WL-WAKE-AP: U11.13 (WL_HOST_WAKE); also elsewhere on the board

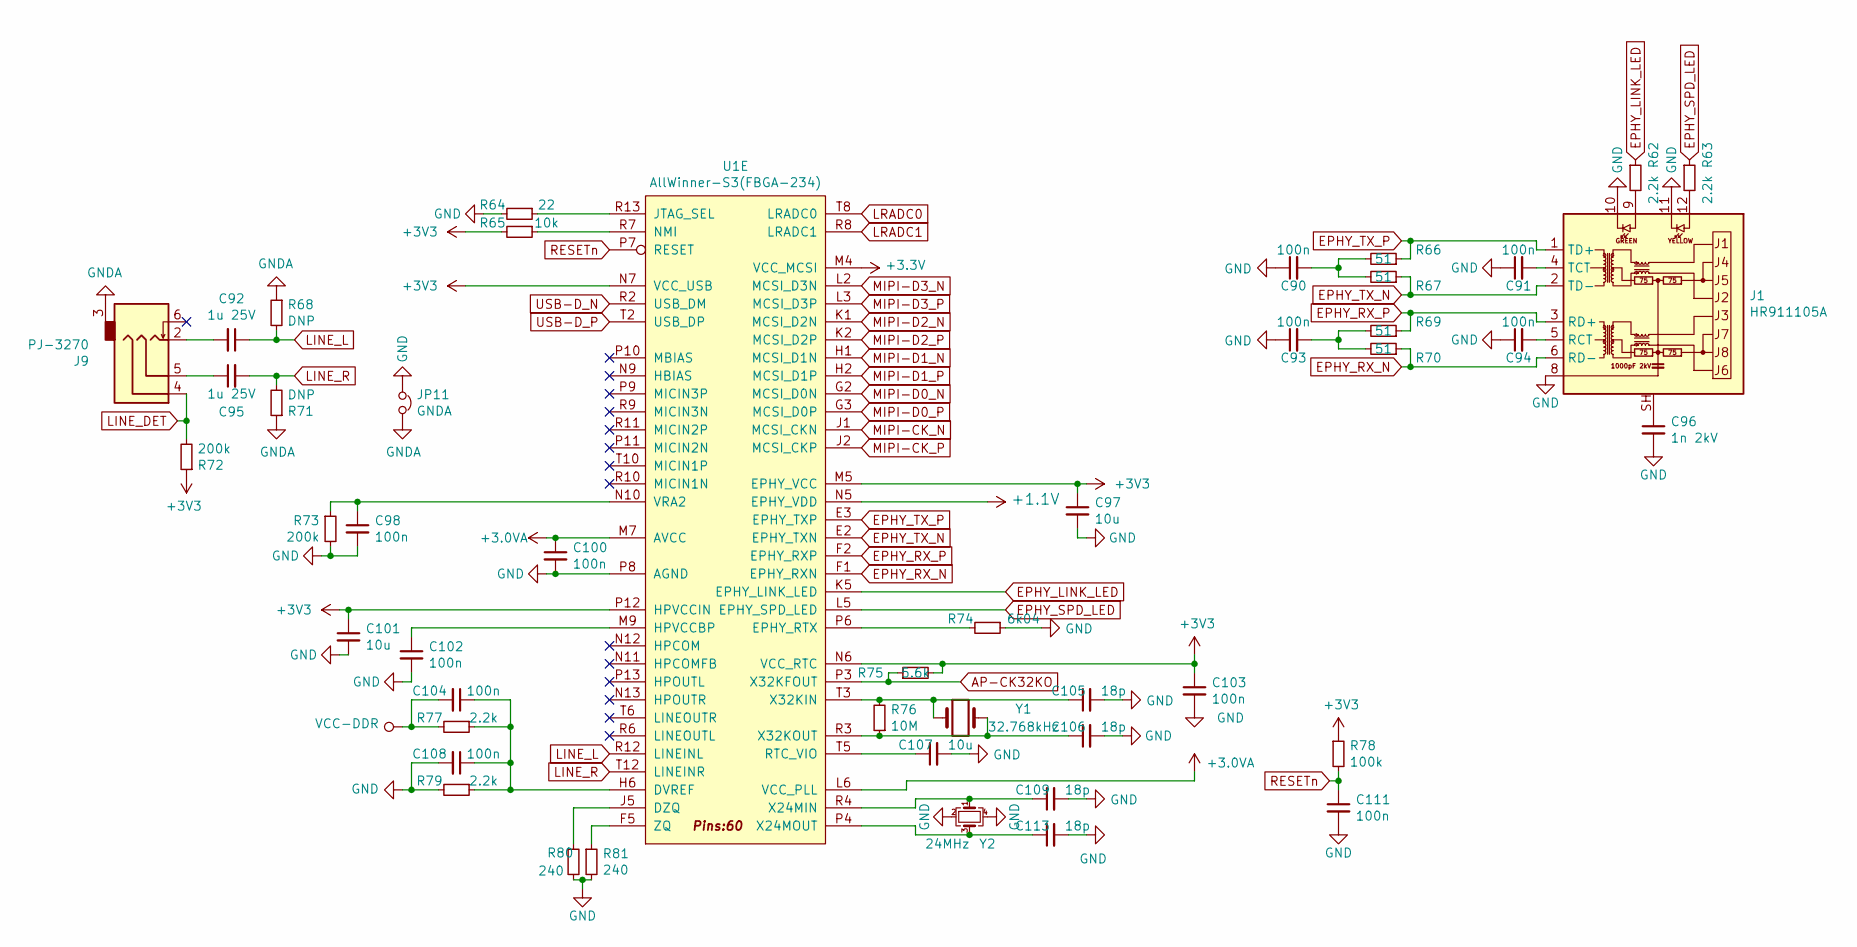
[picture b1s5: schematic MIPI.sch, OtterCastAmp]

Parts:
C90, C91, C93, C94, C98, C100, C102, C103, C104, C108, C111: 100n; C_0402
C92, C95: 1u 25V; C_0603
C96: 1n 2kV; C_1206_3216Metric
C97, C101, C107: 10u; C_0603
C105, C106, C109, C113: 18p; C_0402
J1: HR911105A; RJ45_Hanrun_HR911105A
J9: PJ-3270
JP11: GNDA; SolderJumper-2_P1.3mm_Bridged_Pad1.0x1.5mm
R62, R63, R77, R79: 2.2k; R_0402
R64: 22; R_0402
R65: 10k; R_0402
R66, R67, R69, R70: 51; R_0402
R68, R71: DNP; R_0402
R72, R73: 200k; R_0402
R74: 6k04; R_0402
R75: 5.6k; R_0402
R76: 10M; R_0402
R78: 100k; R_0402
R80, R81: 240; R_0402
U1: AllWinner-S3(FBGA-234); FBGA-234(Pitch-0.65mm_Pad-0.3mm_11x11x1.08mm)
Y1: 32.768kHz; Crystal_SMD_3215-2Pin_3.2x1.5mm
Y2: 24MHz; Oscillator_3225

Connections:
+1.1V: U1.N5 (EPHY_VDD); also elsewhere on the board
+1V5: C104.2, R77.2; also elsewhere on the board
+3.0VA: C100.1, U1.L6 (VCC_PLL), U1.M7 (AVCC); also elsewhere on the board
AP-CK32KO: R75.1, U1.P3 (X32KFOUT); also elsewhere on the board
EPHY_LINK_LED: R62.1, U1.K5 (EPHY_LINK_LED)
EPHY_RX_N: J1.6 (RD-), R70.1, U1.F1 (EPHY_RXN)
EPHY_RX_P: J1.3 (RD+), R69.1, U1.F2 (EPHY_RXP)
EPHY_SPD_LED: R63.1, U1.L5 (EPHY_SPD_LED)
EPHY_TX_N: J1.2 (TD-), R67.1, U1.E2 (EPHY_TXN)
EPHY_TX_P: J1.1 (TD+), R66.1, U1.E3 (EPHY_TXP)
GND: C90.1, C91.1, C93.1, C94.1, C96.2, C97.2, C98.2, C100.2, C101.2, C102.2, C103.2, C105.2, C106.2, C107.2, C108.2, C109.2, C111.2, C113.2, J1.8, J1.10, J1.11, JP11.1, R64.2, R73.2, R74.1, R79.2, R80.2, R81.2, U1.P8 (AGND), Y2.2, Y2.4; also elsewhere on the board
GNDA: J9.3, JP11.2, R68.1, R71.1
LINE_DET: J9.4, R72.2; also elsewhere on the board
LINE_L: C92.1, R68.2, U1.R12 (LINEINL)
LINE_R: C95.2, R71.2, U1.T12 (LINEINR)
LRADC0: U1.T8 (LRADC0)
LRADC1: U1.R8 (LRADC1)
MIPI-CK_N: U1.J1 (MCSI_CKN)
MIPI-CK_P: U1.J2 (MCSI_CKP)
MIPI-D0_N: U1.G2 (MCSI_D0N)
MIPI-D0_P: U1.G3 (MCSI_D0P)
MIPI-D1_N: U1.H1 (MCSI_D1N)
MIPI-D1_P: U1.H2 (MCSI_D1P)
MIPI-D2_N: U1.K1 (MCSI_D2N)
MIPI-D2_P: U1.K2 (MCSI_D2P)
MIPI-D3_N: U1.L2 (MCSI_D3N)
MIPI-D3_P: U1.L3 (MCSI_D3P)
unnamed: C90.2, R66.2, R67.2
unnamed: C91.2, J1.4 (TCT)
unnamed: C92.2, J9.2
unnamed: C93.2, R69.2, R70.2
unnamed: C94.2, J1.5 (RCT)
unnamed: C95.1, J9.5
unnamed: C96.1, J1.SH
unnamed: C98.1, R73.1, U1.N10 (VRA2)
unnamed: C102.1, U1.M9 (HPVCCBP)
unnamed: C104.1, C108.1, R77.1, R79.1, U1.H6 (DVREF)
unnamed: C105.1, R76.2, U1.T3 (X32KIN), Y1.1
unnamed: C106.1, R76.1, U1.R3 (X32KOUT), Y1.2
unnamed: C107.1, U1.T5 (RTC_VIO)
unnamed: C109.1, U1.R4 (X24MIN), Y2.1
unnamed: C113.1, U1.P4 (X24MOUT), Y2.3
unnamed: J1.9, R62.2
unnamed: J1.12, R63.2
unnamed: R64.1, U1.R13 (JTAG_SEL)
unnamed: R65.1, U1.R7 (NMI)
unnamed: R74.2, U1.P6 (EPHY_RTX)
unnamed: R80.1, U1.J5 (DZQ)
unnamed: R81.1, U1.F5 (ZQ)
RESETn: C111.1, R78.2, U1.P7 (RESET)
USB-D_N: U1.R2 (USB_DM); also elsewhere on the board
USB-D_P: U1.T2 (USB_DP); also elsewhere on the board

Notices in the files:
README.md:
License:
MIT Licensed HW
